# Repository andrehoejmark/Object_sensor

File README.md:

<h4> Simple distance, width & height of nearby objects. </h4>

<b> keywords </b> = { <i> lidar, raspberry, arduino, stepmotor, tensorflow, convnet, kamera </i> }

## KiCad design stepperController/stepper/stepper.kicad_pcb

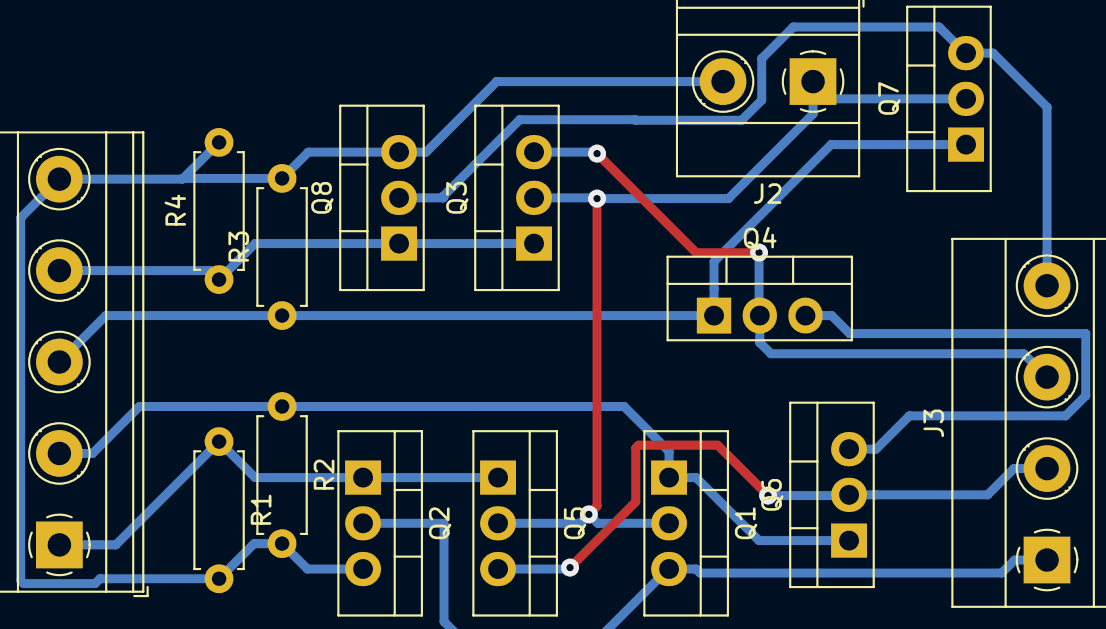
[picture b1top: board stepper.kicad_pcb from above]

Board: 2 copper layers, 15 parts (0 on the bottom side), 10 nets.

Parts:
J1: Conn_01x05_Male; TerminalBlock_Phoenix_MKDS-1,5-5-5.08_1x05_P5.08mm_Horizont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
J2: Conn_01x02_Male; TerminalBlock_Phoenix_MKDS-1,5-2_1x02_P5.00mm_Horizontal
J3: Conn_01x04_Male; TerminalBlock_Phoenix_MKDS-1,5-4-5.08_1x04_P5.08mm_Horizont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
Q1, Q2, Q3, Q4, Q5, Q6, Q7, Q8: Q_NMOS_GDS; TO-220-3_Vertical
R1, R2, R3, R4: R; R_Axial_DIN0207_L6.3mm_D2.5mm_P7.62mm_Horizontal

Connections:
/IN_1_A: J1.1, Q2.1, Q5.1, R1.1
/IN_1_B: J1.2, Q1.1, Q6.1, R2.1
/IN_2_A: J1.3, Q4.1, Q7.1, R3.1
/IN_2_B: J1.4, Q3.1, Q8.1, R4.1
/M1_A: J3.1, Q1.3, Q2.2
/M1_B: J3.2, Q5.3, Q6.2
/M2_A: J3.3, Q3.3, Q4.2
/M2_B: J3.4, Q7.3, Q8.2
GND: J1.5, J2.2, Q2.3, Q4.3, Q6.3, Q8.3, R1.2, R2.2, R3.2, R4.2
VCC: J2.1, Q1.2, Q3.2, Q5.2, Q7.2

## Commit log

2018-11-16 ~python project
2018-11-21 Yolo, SSD and Haar Cascade object detectors
2018-11-23 webbcsm
2018-11-23 3D to 2D camera view projection
2018-11-29 Projection and Detection
2018-11-29 Included distance
2018-12-02 Correction
2018-12-04 This is the tensorflow running on the raspberry pi
2018-12-09 Arduino + python code for LIDAR
2018-12-10 - python dependencies
2018-12-18 lidar sweep in range of start degree, end degrees
2018-12-18 Driver code for the newly built stepper driver + kicad design
2018-12-18 ~actual arduino code
2018-12-18 x1x2_to_width
2018-12-18 asdf
2018-12-19 Sends "None" when changing rotation
    Needed to know when the lidar has sent one array.
2018-12-19 same
2018-12-19 new simple width detection
